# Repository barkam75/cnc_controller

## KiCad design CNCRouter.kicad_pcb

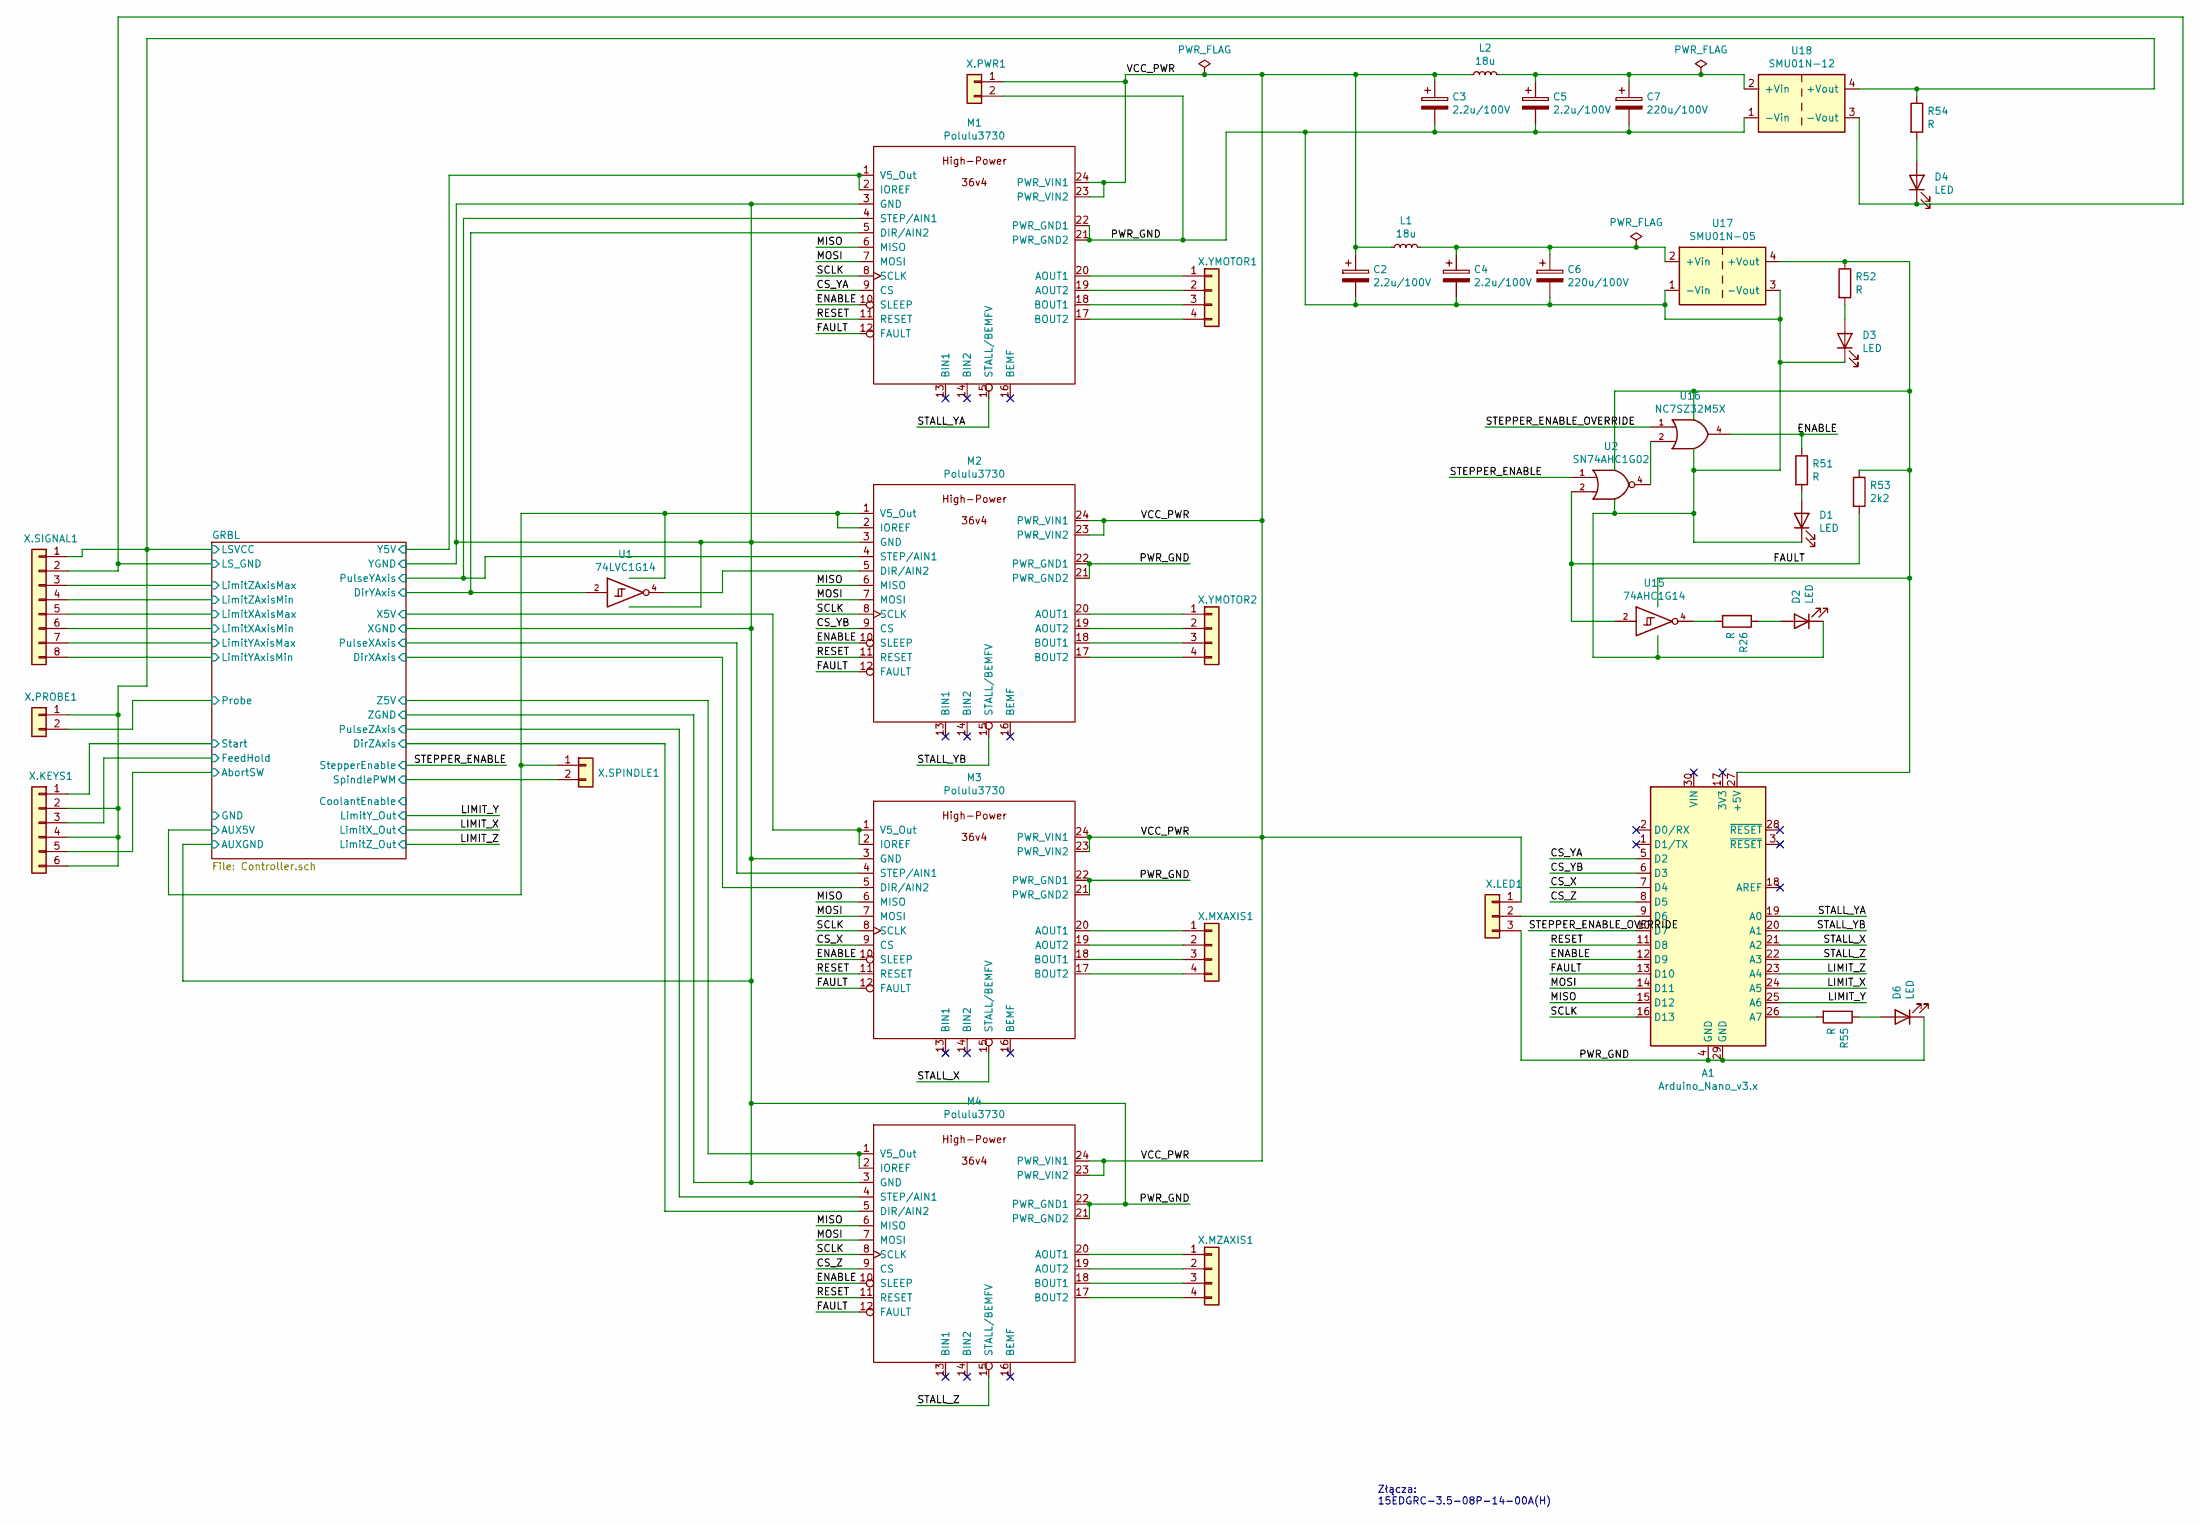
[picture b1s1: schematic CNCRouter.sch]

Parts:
A1: Arduino_Nano_v3.x; Arduino_Nano
C2, C3, C4, C5: 2.2u/100V
C6, C7: 220u/100V
D1, D2, D3, D4, D6: LED; LED_1206_3216Metric_Pad1.42x1.75mm_HandSolder
L1, L2: 18u; L_0805_2012Metric_Pad1.15x1.40mm_HandSolder
M1, M2, M3, M4: Polulu3730; Polulu-3730
R26, R54, R55: R; R_1206_3216Metric_Pad1.30x1.75mm_HandSolder
R51, R52: R; R_0805_2012Metric_Pad1.20x1.40mm_HandSolder
R53: 2k2; R_0805_2012Metric_Pad1.20x1.40mm_HandSolder
U1: 74LVC1G14; SOT-23-5_HandSoldering
U2: SN74AHC1G02; SOT-23-5_HandSoldering
U15: 74AHC1G14; SOT-23-5_HandSoldering
U16: NC7SZ32M5X; SOT-23-5_HandSoldering
U17: SMU01N-05
U18: SMU01N-12
X.KEYS1: Conn_01x06; PhoenixContact_MCV_1,5_6-G-3.5_1x06_P3.50mm_Vertical
X.LED1: Conn_01x03; PhoenixContact_MCV_1,5_3-G-3.5_1x03_P3.50mm_Vertical
X.MXAXIS1, X.MZAXIS1, X.YMOTOR1, X.YMOTOR2: Conn_01x04; PhoenixContact_MCV_1,5_4-G-3.5_1x04_P3.50mm_Vertical
X.PROBE1, X.PWR1, X.SPINDLE1: Conn_01x02; PhoenixContact_MCV_1,5_2-G-3.5_1x02_P3.50mm_Vertical
X.SIGNAL1: Conn_01x08; PhoenixContact_MCV_1,5_8-G-3.5_1x08_P3.50mm_Vertical

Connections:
/CS_X: A1.7 (D4), M3.9 (CS)
/CS_YA: A1.5 (D2), M1.9 (CS)
/CS_YB: A1.6 (D3), M2.9 (CS)
/CS_Z: A1.8 (D5), M4.9 (CS)
/ENABLE: A1.12 (D9), M1.10 (SLEEP), M2.10 (SLEEP), M3.10 (SLEEP), M4.10 (SLEEP), R51.1, U16.4
/FAULT: A1.13 (D10), M1.12 (FAULT), M2.12 (FAULT), M3.12 (FAULT), M4.12 (FAULT), R53.2, U2.2, U15.2
/GRBL/AbortSW: X.KEYS1.5; also elsewhere on the board
/GRBL/DirXAxis: M3.5 (DIR/AIN2); also elsewhere on the board
/GRBL/DirYAxis: M1.5 (DIR/AIN2), U1.2; also elsewhere on the board
/GRBL/DirZAxis: M4.5 (DIR/AIN2); also elsewhere on the board
/GRBL/FeedHold: X.KEYS1.3; also elsewhere on the board
/GRBL/LSVCC: R54.1, U18.4 (+Vout), X.KEYS1.2, X.KEYS1.4, X.KEYS1.6, X.PROBE1.1, X.SIGNAL1.1; also elsewhere on the board
/GRBL/LS_GND: D4.1 (K), U18.3 (-Vout), X.SIGNAL1.2; also elsewhere on the board
/GRBL/LimitXAxisMax: X.SIGNAL1.5; also elsewhere on the board
/GRBL/LimitXAxisMin: X.SIGNAL1.6; also elsewhere on the board
/GRBL/LimitYAxisMax: X.SIGNAL1.7; also elsewhere on the board
/GRBL/LimitYAxisMin: X.SIGNAL1.8; also elsewhere on the board
/GRBL/LimitZAxisMax: X.SIGNAL1.3; also elsewhere on the board
/GRBL/LimitZAxisMin: X.SIGNAL1.4; also elsewhere on the board
/GRBL/Probe: X.PROBE1.2; also elsewhere on the board
/GRBL/PulseXAxis: M3.4 (STEP/AIN1); also elsewhere on the board
/GRBL/PulseYAxis: M1.4 (STEP/AIN1), M2.4 (STEP/AIN1); also elsewhere on the board
/GRBL/PulseZAxis: M4.4 (STEP/AIN1); also elsewhere on the board
/GRBL/SpindlePWM: X.SPINDLE1.2; also elsewhere on the board
/GRBL/Start: X.KEYS1.1; also elsewhere on the board
/GRBL/X5V: M3.1 (V5_Out), M3.2 (IOREF); also elsewhere on the board
/GRBL/Y5V: M1.1 (V5_Out), M1.2 (IOREF); also elsewhere on the board
/GRBL/Z5V: M4.1 (V5_Out), M4.2 (IOREF); also elsewhere on the board
/LIMIT_X: A1.24 (A5); also elsewhere on the board
/LIMIT_Y: A1.25 (A6); also elsewhere on the board
/LIMIT_Z: A1.23 (A4); also elsewhere on the board
/MISO: A1.15 (D12), M1.6 (MISO), M2.6 (MISO), M3.6 (MISO), M4.6 (MISO)
/MOSI: A1.14 (D11), M1.7 (MOSI), M2.7 (MOSI), M3.7 (MOSI), M4.7 (MOSI)
/RESET: A1.11 (D8), M1.11 (RESET), M2.11 (RESET), M3.11 (RESET), M4.11 (RESET)
/SCLK: A1.16 (D13), M1.8 (SCLK), M2.8 (SCLK), M3.8 (SCLK), M4.8 (SCLK)
/STALL_X: A1.21 (A2), M3.15 (STALL/BEMFV)
/STALL_YA: A1.19 (A0), M1.15 (STALL/BEMFV)
/STALL_YB: A1.20 (A1), M2.15 (STALL/BEMFV)
/STALL_Z: A1.22 (A3), M4.15 (STALL/BEMFV)
/STEPPER_ENABLE: U2.1; also elsewhere on the board
/STEPPER_ENABLE_OVERRIDE: A1.10 (D7), U16.1
/VCC_PWR: C2.1, C3.1, L1.1, L2.1, M1.23 (PWR_VIN2), M1.24 (PWR_VIN1), M2.23 (PWR_VIN2), M2.24 (PWR_VIN1), M3.23 (PWR_VIN2), M3.24 (PWR_VIN1), M4.23 (PWR_VIN2), M4.24 (PWR_VIN1), X.LED1.1, X.PWR1.1
GND: A1.4 (GND), A1.29 (GND), C2.2, C3.2, C4.2, C5.2, C6.2, C7.2, D1.1 (K), D2.1 (K), D3.1 (K), D6.1 (K), M1.3 (GND), M1.21 (PWR_GND2), M1.22 (PWR_GND1), M2.3 (GND), M2.21 (PWR_GND2), M2.22 (PWR_GND1), M3.3 (GND), M3.21 (PWR_GND2), M3.22 (PWR_GND1), M4.3 (GND), M4.21 (PWR_GND2), M4.22 (PWR_GND1), U1.3 (GND), U2.3 (GND), U15.3 (GND), U16.3 (GND), U17.1 (-Vin), U17.3 (-Vout), U18.1 (-Vin), X.LED1.3, X.PWR1.2; also elsewhere on the board
unnamed: A1.9 (D6), X.LED1.2
unnamed: A1.26 (A7), R55.2
unnamed: C4.1, C6.1, L1.2, U17.2 (+Vin)
unnamed: C5.1, C7.1, L2.2, U18.2 (+Vin)
unnamed: D1.2 (A), R51.2
unnamed: D2.2 (A), R26.1
unnamed: D3.2 (A), R52.2
unnamed: D4.2 (A), R54.2
unnamed: D6.2 (A), R55.1
unnamed: M1.17 (BOUT2), X.YMOTOR1.4
unnamed: M1.18 (BOUT1), X.YMOTOR1.3
unnamed: M1.19 (AOUT2), X.YMOTOR1.2
unnamed: M1.20 (AOUT1), X.YMOTOR1.1
unnamed: M2.5 (DIR/AIN2), U1.4
unnamed: M2.17 (BOUT2), X.YMOTOR2.4
unnamed: M2.18 (BOUT1), X.YMOTOR2.3
unnamed: M2.19 (AOUT2), X.YMOTOR2.2
unnamed: M2.20 (AOUT1), X.YMOTOR2.1
unnamed: M3.17 (BOUT2), X.MXAXIS1.4
unnamed: M3.18 (BOUT1), X.MXAXIS1.3
unnamed: M3.19 (AOUT2), X.MXAXIS1.2
unnamed: M3.20 (AOUT1), X.MXAXIS1.1
unnamed: M4.17 (BOUT2), X.MZAXIS1.4
unnamed: M4.18 (BOUT1), X.MZAXIS1.3
unnamed: M4.19 (AOUT2), X.MZAXIS1.2
unnamed: M4.20 (AOUT1), X.MZAXIS1.1
unnamed: R26.2, U15.4
unnamed: U2.4, U16.2

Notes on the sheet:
Złącza: 15EDGRC-3.5-08P-14-00A(H)

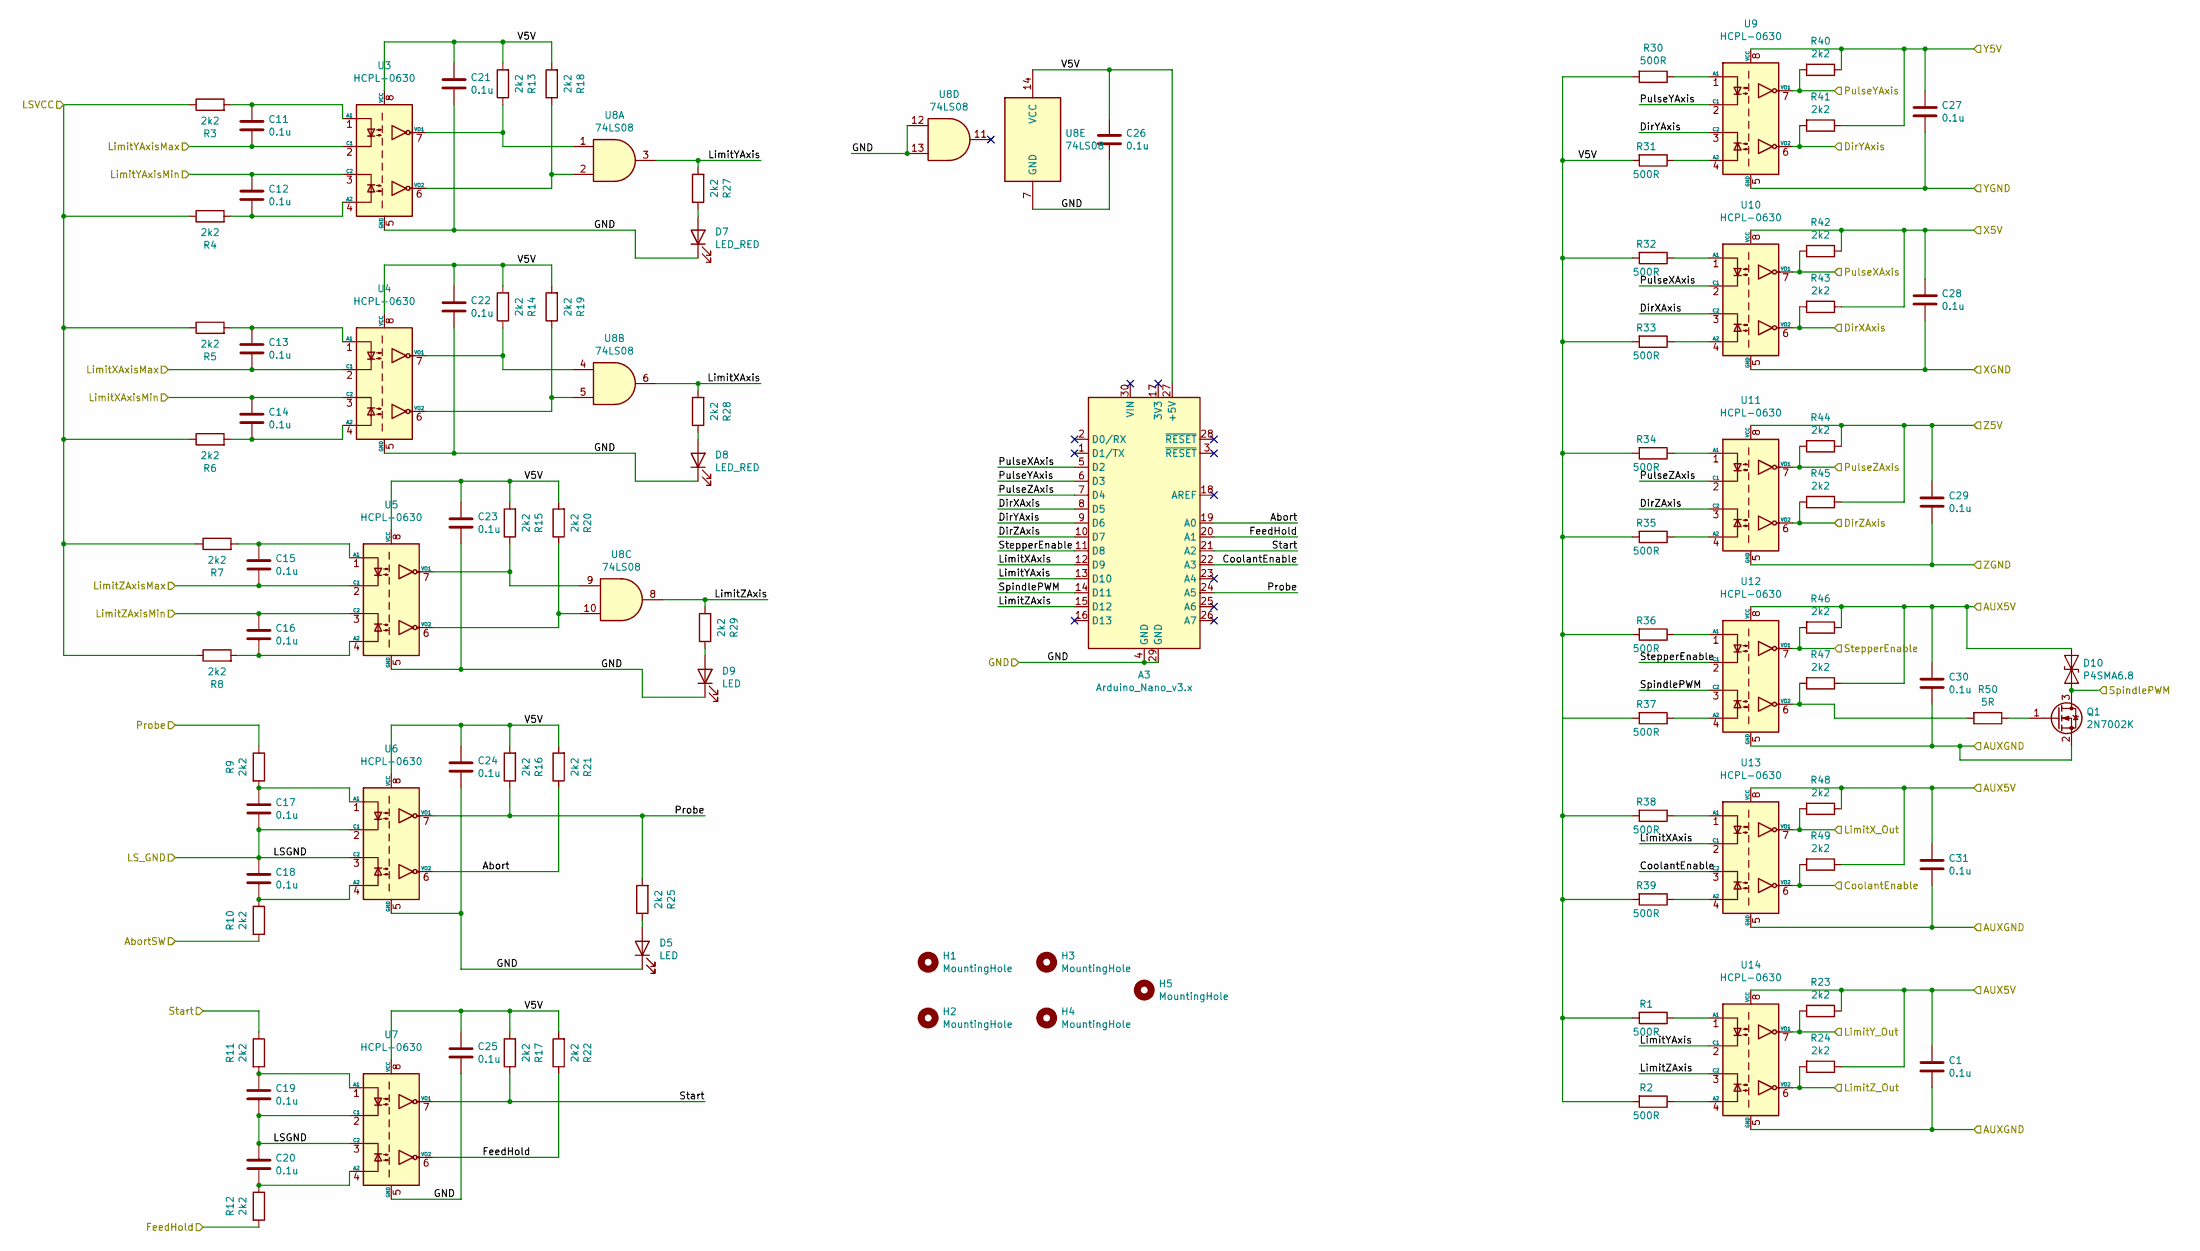
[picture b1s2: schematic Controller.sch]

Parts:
A3: Arduino_Nano_v3.x; Arduino_Nano
C1, C11, C12, C13, C14, C15, C16, C17, C18, C19, C20, C21, C22, C23, C24, C25, C26, C27, C28, C29, C30, C31: 0.1u; C_0805_2012Metric_Pad1.18x1.45mm_HandSolder
D5, D9: LED; LED_1206_3216Metric_Pad1.42x1.75mm_HandSolder
D7, D8: LED_RED; LED_1206_3216Metric_Pad1.42x1.75mm_HandSolder
D10: P4SMA6.8; D_SOD-323
H1, H2, H3, H4, H5: MountingHole; MountingHole_3.7mm_Pad_Via
Q1: 2N7002K; SOT-23
R1, R2, R30, R31, R32, R33, R34, R35, R36, R37, R38, R39: 500R; R_0805_2012Metric_Pad1.20x1.40mm_HandSolder
R3, R4, R5, R6, R7, R8, R9, R10, R11, R12, R13, R14, R15, R16, R17, R18, R19, R20, R21, R22, R23, R24, R25, R27, R28, R29, R40, R41, R42, R43, R44, R45, R46, R47, R48, R49: 2k2; R_0805_2012Metric_Pad1.20x1.40mm_HandSolder
R50: 5R; R_0805_2012Metric_Pad1.20x1.40mm_HandSolder
U3, U4, U5, U6, U7, U9, U10, U11, U12, U13, U14: HCPL-0630; SOIC-8_3.9x4.9mm_P1.27mm
U8: 74LS08; SOIC-14_3.9x8.7mm_P1.27mm

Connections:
/GRBL/Abort: A3.19 (A0), R21.1, U6.6 (VO2)
/GRBL/AbortSW: R10.2; also elsewhere on the board
/GRBL/CoolantEnable: A3.22 (A3), R49.2, U13.3 (C2), U13.6 (VO2)
/GRBL/DirXAxis: A3.8 (D5), R43.2, U10.3 (C2), U10.6 (VO2); also elsewhere on the board
/GRBL/DirYAxis: A3.9 (D6), R41.2, U9.3 (C2), U9.6 (VO2); also elsewhere on the board
/GRBL/DirZAxis: A3.10 (D7), R45.2, U11.3 (C2), U11.6 (VO2); also elsewhere on the board
/GRBL/FeedHold: A3.20 (A1), R12.2, R22.1, U7.6 (VO2); also elsewhere on the board
/GRBL/LSVCC: R3.1, R4.1, R5.1, R6.1, R7.1, R8.1; also elsewhere on the board
/GRBL/LS_GND: C17.2, C18.1, C19.2, C20.1, U6.2 (C1), U6.3 (C2), U7.2 (C1), U7.3 (C2); also elsewhere on the board
/GRBL/LimitXAxis: A3.12 (D9), R28.2, U8.6, U13.2 (C1)
/GRBL/LimitXAxisMax: C13.2, U4.2 (C1); also elsewhere on the board
/GRBL/LimitXAxisMin: C14.1, U4.3 (C2); also elsewhere on the board
/GRBL/LimitYAxis: A3.13 (D10), R27.2, U8.3, U14.2 (C1)
/GRBL/LimitYAxisMax: C11.2, U3.2 (C1); also elsewhere on the board
/GRBL/LimitYAxisMin: C12.1, U3.3 (C2); also elsewhere on the board
/GRBL/LimitZAxis: A3.15 (D12), R29.2, U8.8, U14.3 (C2)
/GRBL/LimitZAxisMax: C15.2, U5.2 (C1); also elsewhere on the board
/GRBL/LimitZAxisMin: C16.1, U5.3 (C2); also elsewhere on the board
/GRBL/Probe: A3.24 (A5), R9.1, R16.1, R25.2, U6.7 (VO1); also elsewhere on the board
/GRBL/PulseXAxis: A3.5 (D2), R42.2, U10.2 (C1), U10.7 (VO1); also elsewhere on the board
/GRBL/PulseYAxis: A3.6 (D3), R40.2, U9.2 (C1), U9.7 (VO1); also elsewhere on the board
/GRBL/PulseZAxis: A3.7 (D4), R44.2, U11.2 (C1), U11.7 (VO1); also elsewhere on the board
/GRBL/SpindlePWM: A3.14 (D11), D10.2 (A2), Q1.3 (D), U12.3 (C2); also elsewhere on the board
/GRBL/Start: A3.21 (A2), R11.1, R17.1, U7.7 (VO1); also elsewhere on the board
/GRBL/V5V: A3.27 (+5V), C21.1, C22.1, C23.1, C24.1, C25.1, C26.1, R1.2, R2.2, R13.2, R14.2, R15.2, R16.2, R17.2, R18.2, R19.2, R20.2, R21.2, R22.2, R30.2, R31.2, R32.2, R33.2, R34.2, R35.2, R36.2, R37.2, R38.2, R39.2, U3.8 (VCC), U4.8 (VCC), U5.8 (VCC), U6.8 (VCC), U7.8 (VCC), U8.14 (VCC)
/GRBL/X5V: C28.1, R42.1, R43.1, U10.8 (VCC); also elsewhere on the board
/GRBL/Y5V: C27.1, R40.1, R41.1, U9.8 (VCC); also elsewhere on the board
/GRBL/Z5V: C29.1, R44.1, R45.1, U11.8 (VCC); also elsewhere on the board
/LIMIT_X: R48.2, U13.7 (VO1); also elsewhere on the board
/LIMIT_Y: R23.2, U14.7 (VO1); also elsewhere on the board
/LIMIT_Z: R24.2, U14.6 (VO2); also elsewhere on the board
/STEPPER_ENABLE: A3.11 (D8), R46.2, U12.2 (C1), U12.7 (VO1); also elsewhere on the board
GND: A3.4 (GND), A3.29 (GND), C1.2, C21.2, C22.2, C23.2, C24.2, C25.2, C26.2, C27.2, C28.2, C29.2, C30.2, C31.2, D5.1 (K), D7.1 (K), D8.1 (K), D9.1 (K), Q1.2 (S), U3.5 (GND), U4.5 (GND), U5.5 (GND), U6.5 (GND), U7.5 (GND), U8.7 (GND), U8.12, U8.13, U9.5 (GND), U10.5 (GND), U11.5 (GND), U12.5 (GND), U13.5 (GND), U14.5 (GND); also elsewhere on the board
unnamed: C11.1, R3.2, U3.1 (A1)
unnamed: C12.2, R4.2, U3.4 (A2)
unnamed: C13.1, R5.2, U4.1 (A1)
unnamed: C14.2, R6.2, U4.4 (A2)
unnamed: C15.1, R7.2, U5.1 (A1)
unnamed: C16.2, R8.2, U5.4 (A2)
unnamed: C17.1, R9.2, U6.1 (A1)
unnamed: C18.2, R10.1, U6.4 (A2)
unnamed: C19.1, R11.2, U7.1 (A1)
unnamed: C20.2, R12.1, U7.4 (A2)
unnamed: D5.2 (A), R25.1
unnamed: D7.2 (A), R27.1
unnamed: D8.2 (A), R28.1
unnamed: D9.2 (A), R29.1
unnamed: Q1.1 (G), R50.1
unnamed: R1.1, U14.1 (A1)
unnamed: R2.1, U14.4 (A2)
unnamed: R13.1, U3.7 (VO1), U8.1
unnamed: R14.1, U4.7 (VO1), U8.4
unnamed: R15.1, U5.7 (VO1), U8.9
unnamed: R18.1, U3.6 (VO2), U8.2
unnamed: R19.1, U4.6 (VO2), U8.5
unnamed: R20.1, U5.6 (VO2), U8.10
unnamed: R30.1, U9.1 (A1)
unnamed: R31.1, U9.4 (A2)
unnamed: R32.1, U10.1 (A1)
unnamed: R33.1, U10.4 (A2)
unnamed: R34.1, U11.1 (A1)
unnamed: R35.1, U11.4 (A2)
unnamed: R36.1, U12.1 (A1)
unnamed: R37.1, U12.4 (A2)
unnamed: R38.1, U13.1 (A1)
unnamed: R39.1, U13.4 (A2)
unnamed: R47.2, R50.2, U12.6 (VO2)

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
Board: 2 copper layers, 127 parts (0 on the bottom side), 110 nets, no tracks yet.
